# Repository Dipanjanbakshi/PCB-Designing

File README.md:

# PCB-Designing
Some practice projects I made while learning PCB designing on Ki Cad!

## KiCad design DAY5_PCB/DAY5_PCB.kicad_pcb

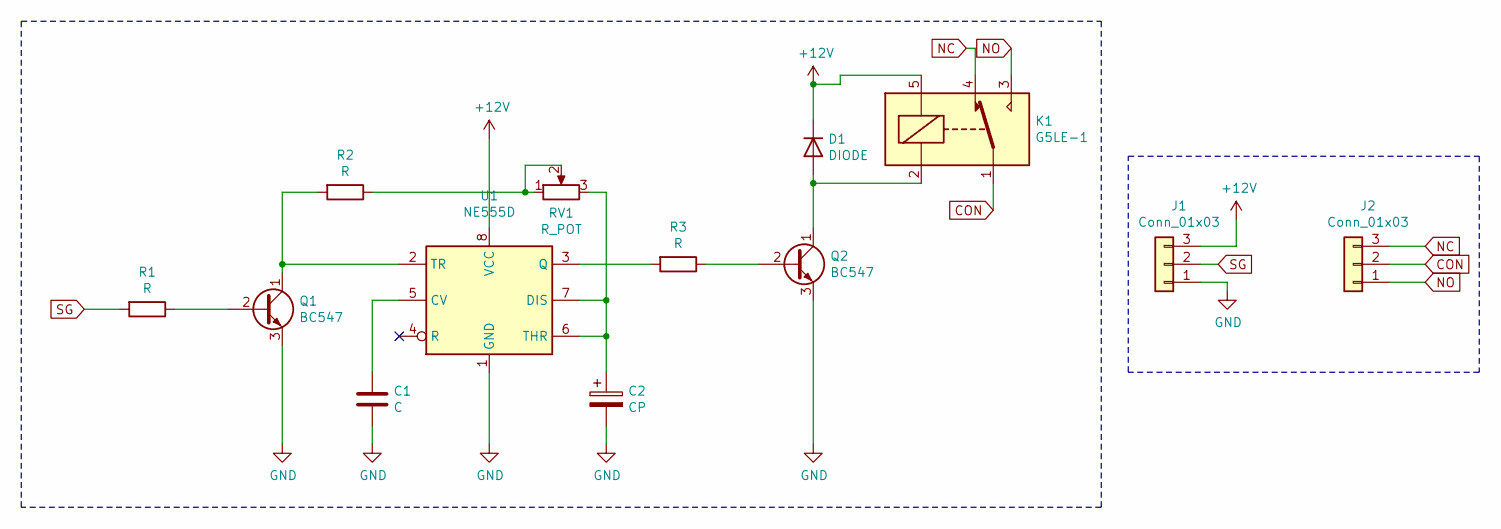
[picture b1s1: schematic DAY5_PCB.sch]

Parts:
C1: C; C_1206_3216Metric_Pad1.33x1.80mm_HandSolder
C2: CP; CP_Radial_D8.0mm_P3.80mm
D1: DIODE; D_1210_3225Metric_Pad1.42x2.65mm_HandSolder
J1, J2: Conn_01x03; PinHeader_1x03_P2.54mm_Vertical
K1: G5LE-1; Relay_SPDT_Omron-G5LE-1
Q1, Q2: BC547; TO-92_Inline
R1, R2, R3: R; R_1206_3216Metric_Pad1.30x1.75mm_HandSolder
RV1: R_POT; Potentiometer_Bourns_3266Y_Vertical
U1: NE555D; SOIC-8_3.9x4.9mm_P1.27mm

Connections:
+12V: D1.2 (K), J1.3, K1.5, U1.8 (VCC)
CON: J2.2, K1.1
GND: C1.2, C2.2, J1.1, Q1.3 (E), Q2.3 (E), U1.1 (GND)
NC: J2.3, K1.4
NO: J2.1, K1.3
unnamed: C1.1, U1.5 (CV)
unnamed: C2.1, RV1.3, U1.6 (THR), U1.7 (DIS)
unnamed: D1.1 (A), K1.2, Q2.1 (C)
unnamed: Q1.1 (C), R2.2, U1.2 (TR)
unnamed: Q1.2 (B), R1.1
unnamed: Q2.2 (B), R3.1
unnamed: R2.1, RV1.1, RV1.2
unnamed: R3.2, U1.3 (Q)
SG: J1.2, R1.2

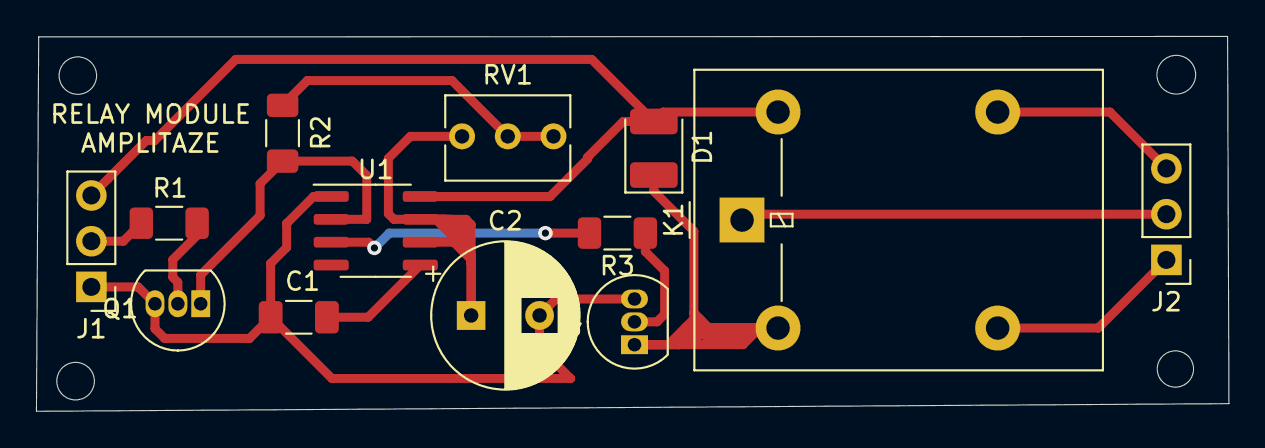
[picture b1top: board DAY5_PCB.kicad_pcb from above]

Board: 2 copper layers, 66.2 x 20.8 mm, 13 parts (0 on the bottom side), 14 nets.

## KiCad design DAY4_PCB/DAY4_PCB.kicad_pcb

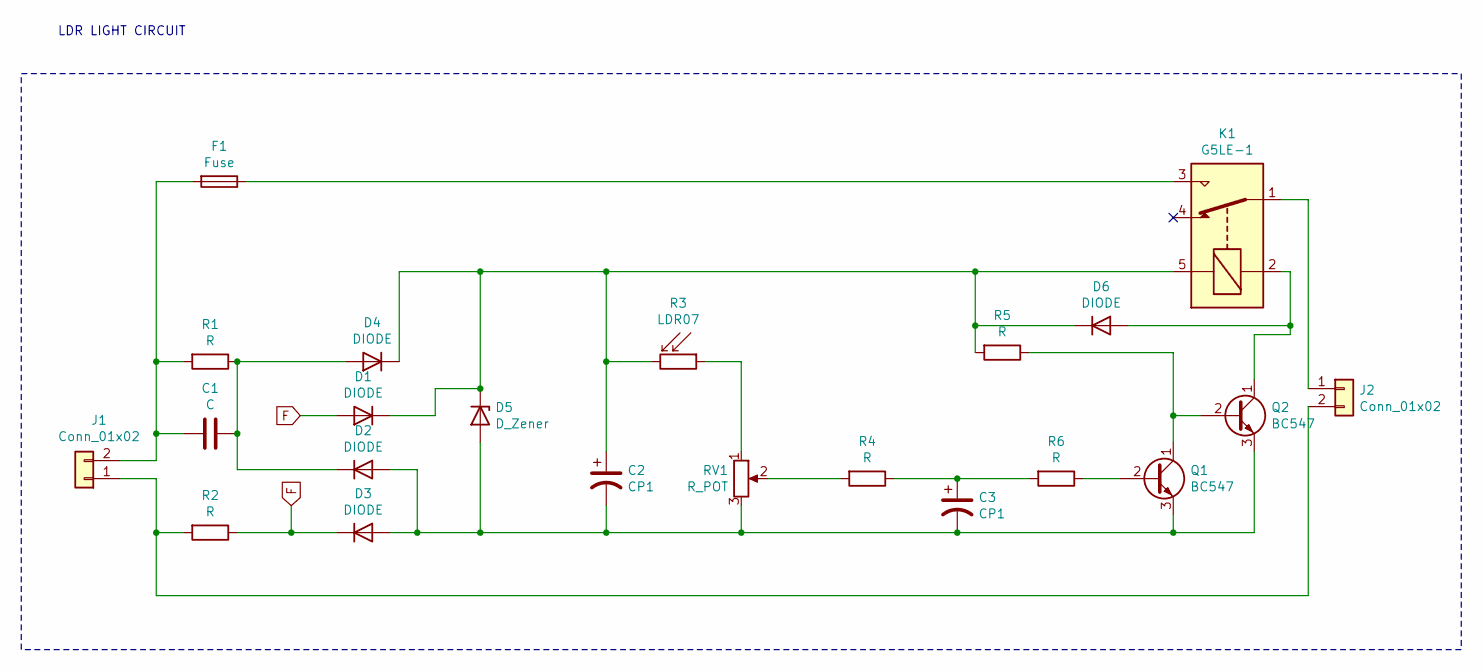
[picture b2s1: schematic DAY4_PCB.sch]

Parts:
C1: C; C_Rect_L13.0mm_W5.0mm_P10.00mm_FKS3_FKP3_MKS4
C2, C3: CP1; CP_Radial_D5.0mm_P2.50mm
D1, D2, D3, D4, D6: DIODE; D_2114_3652Metric_Pad1.85x3.75mm_HandSolder
D5: D_Zener; D_DO-34_SOD68_P10.16mm_Horizontal
F1: Fuse; Fuseholder_Cylinder-5x20mm_Stelvio-Kontek_PTF78_Horizontal_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
J1, J2: Conn_01x02; PhoenixContact_MCV_1,5_2-G-3.5_1x02_P3.50mm_Vertical
K1: G5LE-1; Relay_SPDT_Omron-G5LE-1
Q1, Q2: BC547; TO-92_Inline
R1: R; R_Axial_DIN0614_L14.3mm_D5.7mm_P20.32mm_Horizontal
R2: R; R_Axial_Power_L25.0mm_W6.4mm_P30.48mm
R3: LDR07; R_LDR_5.1x4.3mm_P3.4mm_Vertical
R4, R5, R6: R; R_1206_3216Metric_Pad1.30x1.75mm_HandSolder
RV1: R_POT; Potentiometer_Bourns_3269W_Vertical

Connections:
F: D1.1 (A), D3.2 (K), R2.1
unnamed: C1.1, D2.2 (K), D4.1 (A), R1.1
unnamed: C1.2, F1.2, J1.2, R1.2
unnamed: C2.1, D1.2 (K), D4.2 (K), D5.1 (K), D6.2 (K), K1.5, R3.2, R5.2
unnamed: C2.2, C3.2, D2.1 (A), D3.1 (A), D5.2 (A), Q1.3 (E), Q2.3 (E), RV1.3
unnamed: C3.1, R4.1, R6.2
unnamed: D6.1 (A), K1.2, Q2.1 (C)
unnamed: F1.1, K1.3
unnamed: J1.1, J2.2, R2.2
unnamed: J2.1, K1.1
unnamed: Q1.1 (C), Q2.2 (B), R5.1
unnamed: Q1.2 (B), R6.1
unnamed: R3.1, RV1.1
unnamed: R4.2, RV1.2

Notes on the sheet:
LDR LIGHT CIRCUIT

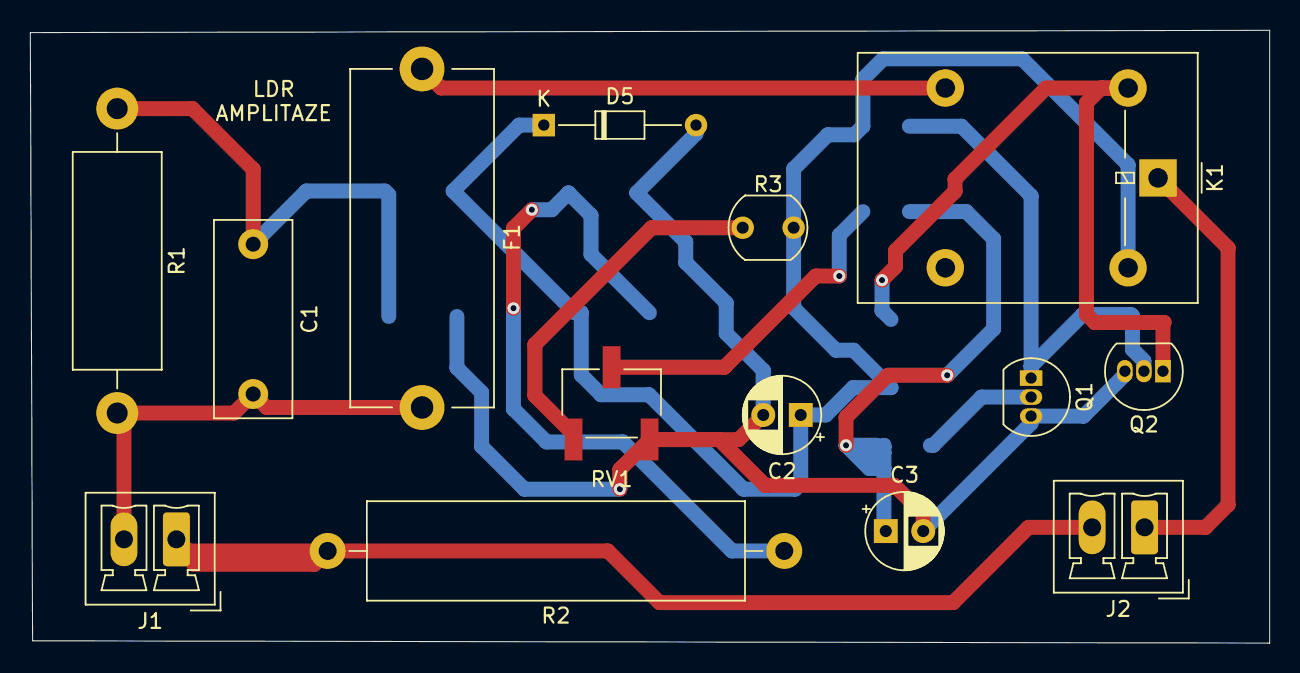
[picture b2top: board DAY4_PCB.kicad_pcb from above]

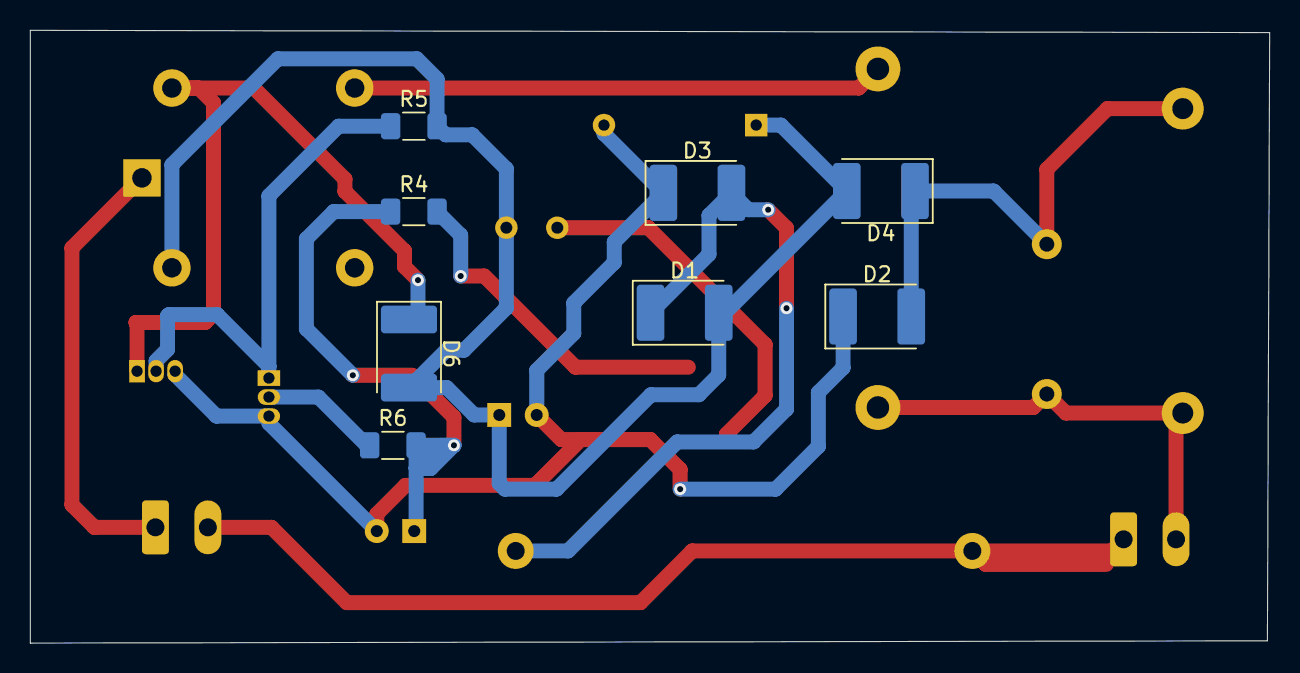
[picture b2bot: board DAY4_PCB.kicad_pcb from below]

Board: 2 copper layers, 82.7 x 40.9 mm, 22 parts (8 on the bottom side), 14 nets.

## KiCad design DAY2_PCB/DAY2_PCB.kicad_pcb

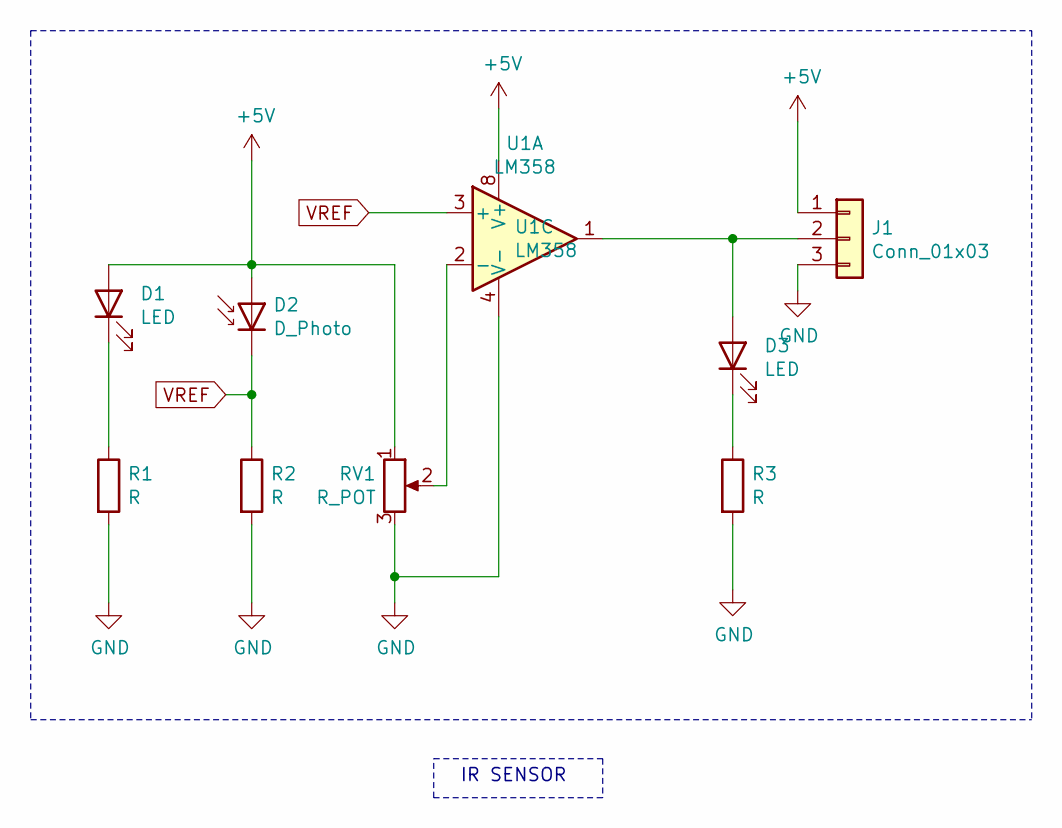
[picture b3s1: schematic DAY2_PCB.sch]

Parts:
D1: LED; LED_D5.0mm_IRGrey
D2: D_Photo; LED_D5.0mm_Clear
D3: LED; LED_1206_3216Metric_Pad1.42x1.75mm_HandSolder
J1: Conn_01x03; PinHeader_1x03_P2.54mm_Vertical
R1, R2, R3: R; R_1206_3216Metric_Pad1.30x1.75mm_HandSolder
RV1: R_POT; Potentiometer_Bourns_3269W_Vertical
U1: LM358; SOIC-8_3.9x4.9mm_P1.27mm

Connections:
+5V: D1.2 (A), D2.2 (A), J1.1, RV1.1, U1.8 (V+)
GND: J1.3, R1.2, R2.2, R3.2, RV1.3, U1.4 (V-)
unnamed: D1.1 (K), R1.1
unnamed: D3.1 (K), R3.1
unnamed: D3.2 (A), J1.2, U1.1
unnamed: RV1.2, U1.2 (-)
VREF: D2.1 (K), R2.1, U1.3 (+)

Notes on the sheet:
IR SENSOR

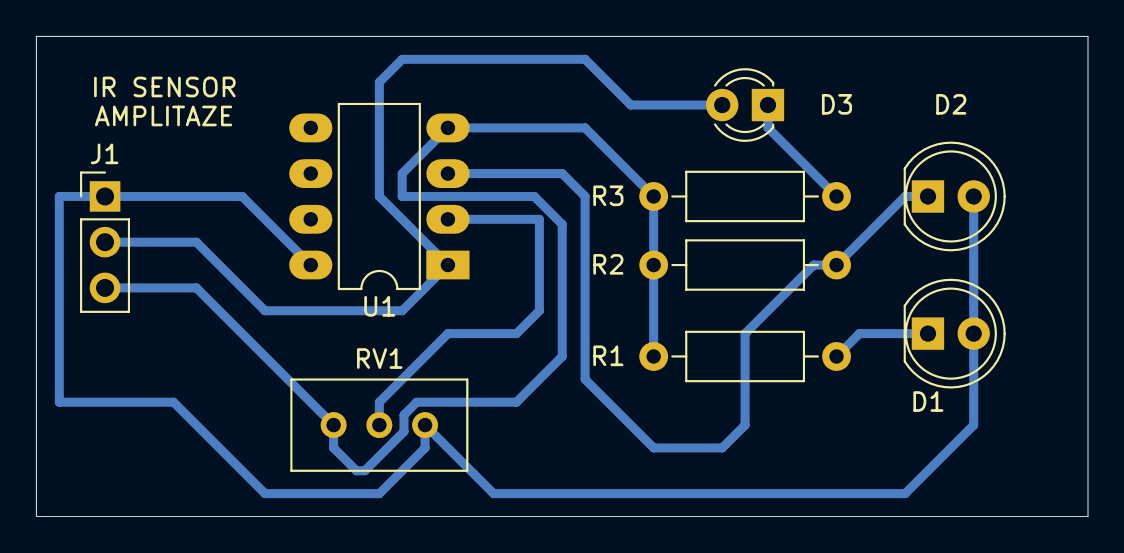
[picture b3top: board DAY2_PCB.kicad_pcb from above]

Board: 2 copper layers, 58.4 x 26.7 mm, 9 parts (0 on the bottom side), 7 nets.

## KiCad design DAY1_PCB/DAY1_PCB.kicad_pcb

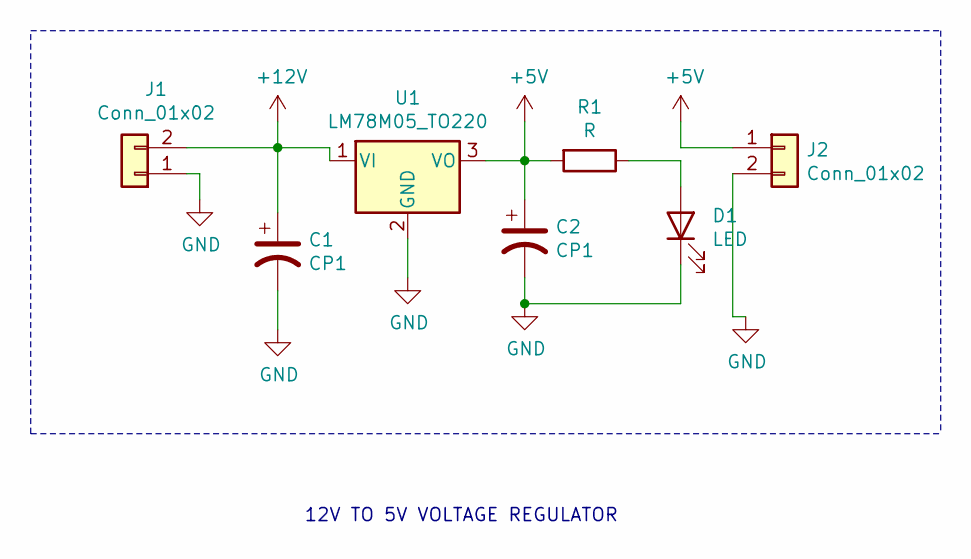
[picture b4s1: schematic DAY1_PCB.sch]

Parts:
C1, C2: CP1; CP_Radial_D6.3mm_P2.50mm
D1: LED; LED_D3.0mm
J1, J2: Conn_01x02; PinHeader_1x02_P2.54mm_Vertical
R1: R; R_Axial_DIN0207_L6.3mm_D2.5mm_P10.16mm_Horizontal
U1: LM78M05_TO220; TO-220-3_Vertical

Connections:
+5V: C2.1, J2.1, R1.2, U1.3 (VO)
+12V: C1.1, J1.2, U1.1 (VI)
GND: C1.2, C2.2, D1.1 (K), J1.1, J2.2, U1.2 (GND)
unnamed: D1.2 (A), R1.1

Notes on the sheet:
12V TO 5V VOLTAGE REGULATOR

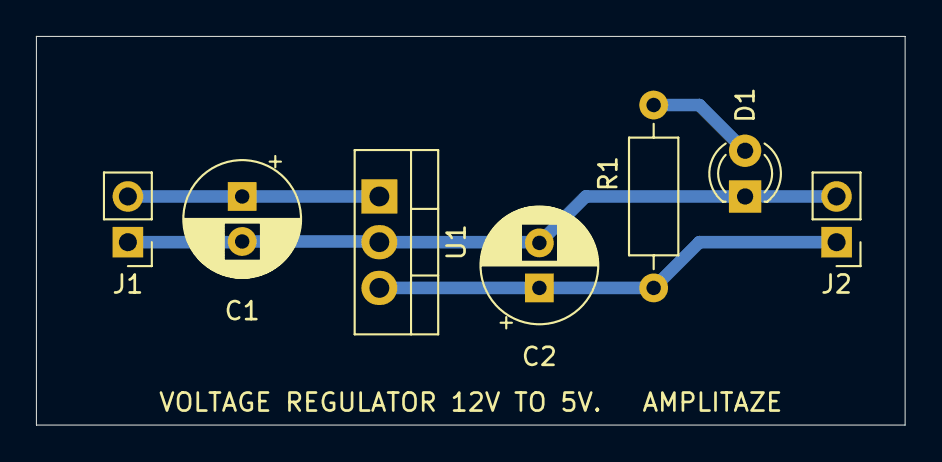
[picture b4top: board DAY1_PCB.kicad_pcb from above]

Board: 2 copper layers, 48.3 x 21.6 mm, 7 parts (0 on the bottom side), 4 nets.

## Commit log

2022-01-16 Initial commit.
    Uploading files.
